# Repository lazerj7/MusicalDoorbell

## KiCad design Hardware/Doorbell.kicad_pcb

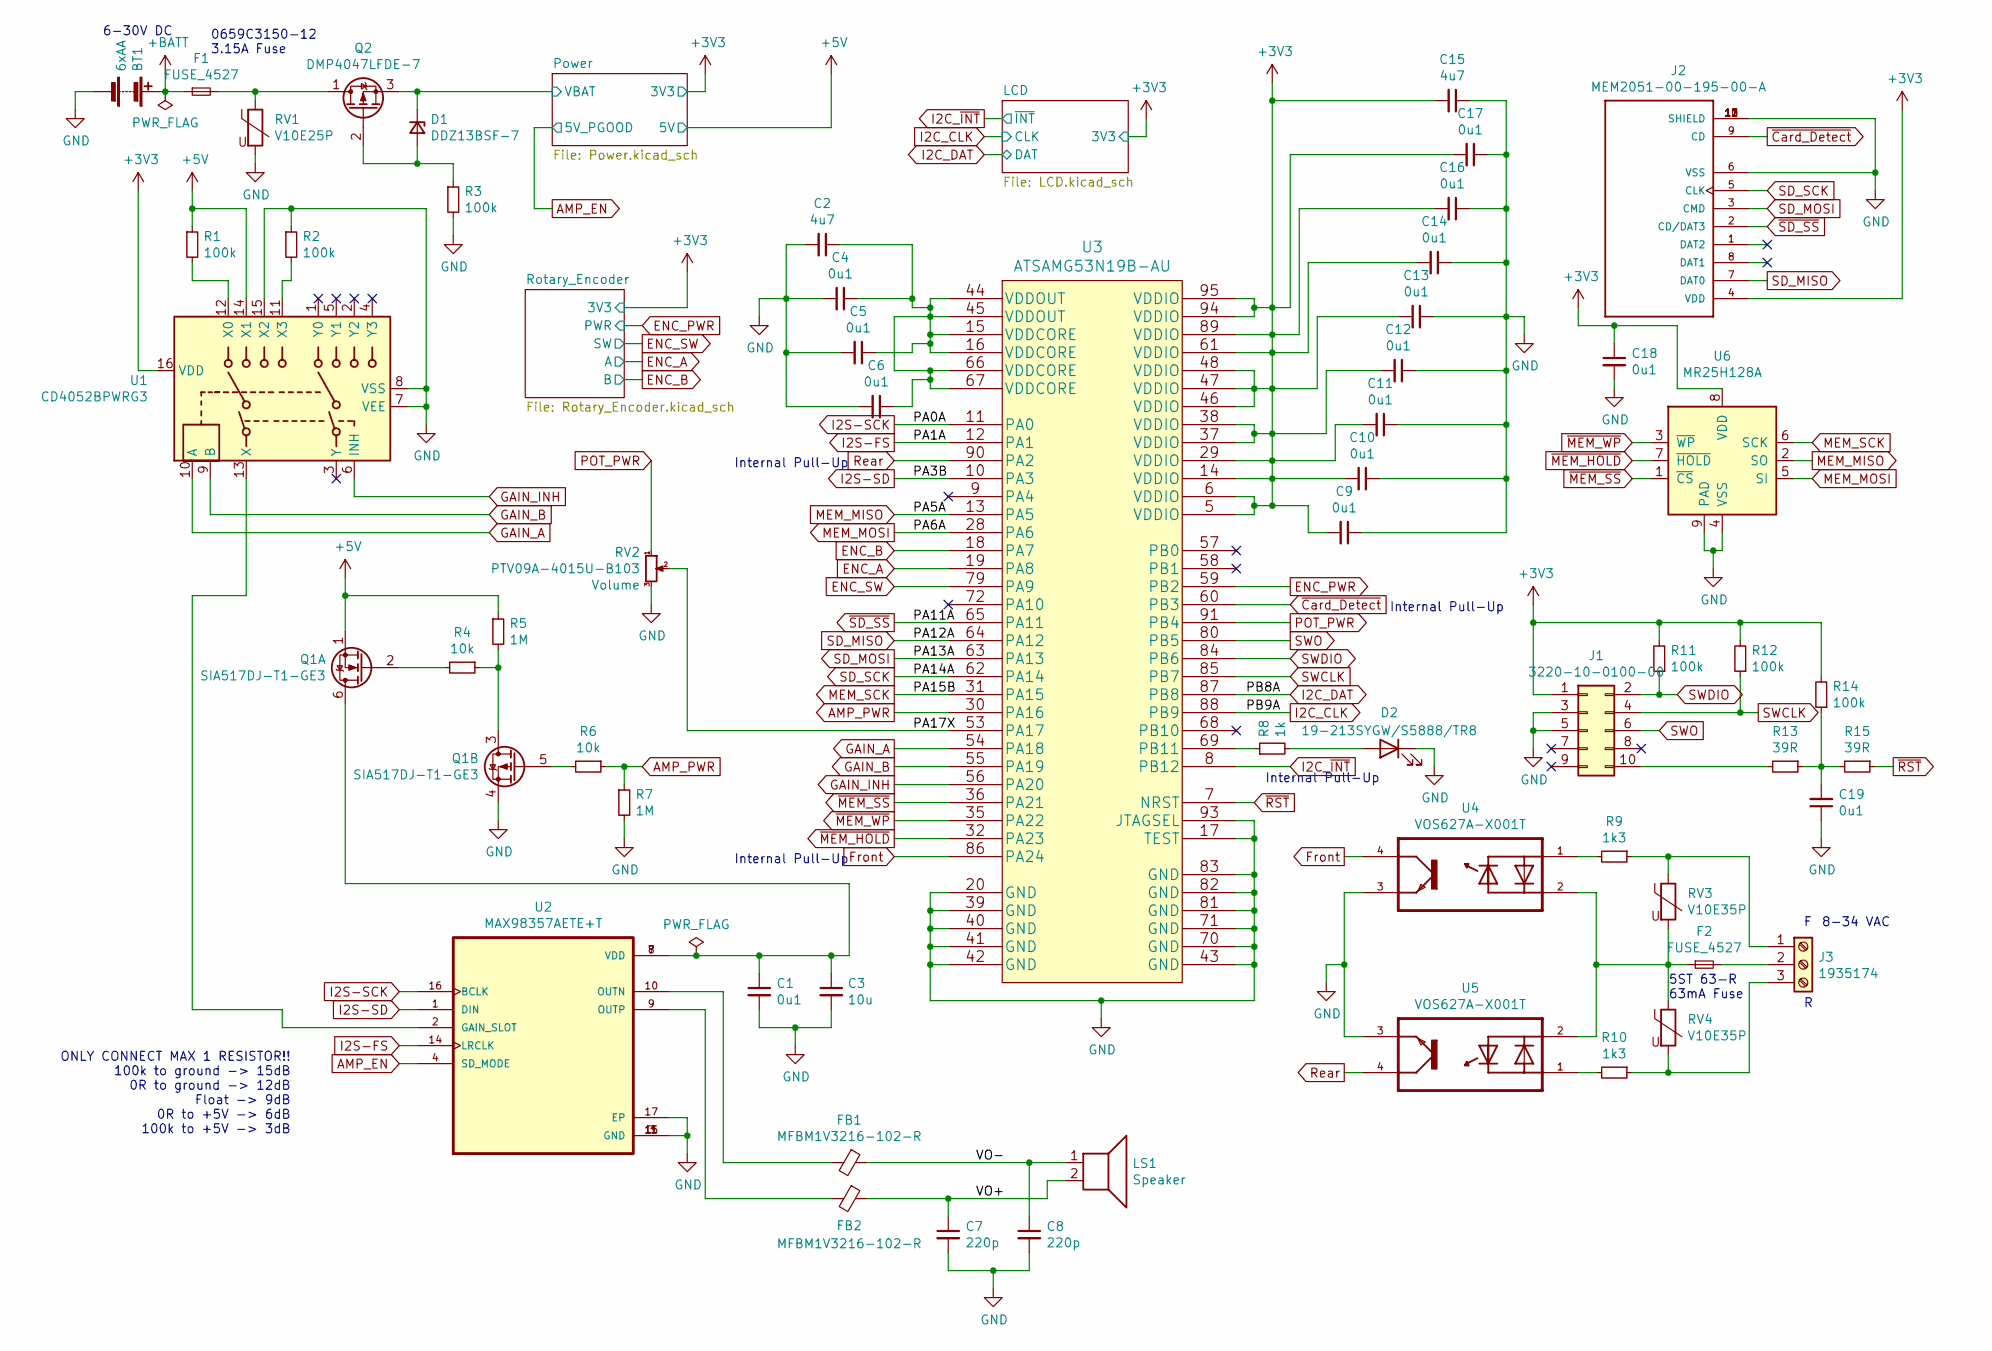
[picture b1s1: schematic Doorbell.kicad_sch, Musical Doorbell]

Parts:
BT1: 6xAA; Molex_MicroClasp_55935-0210_1x02_P2.00mm_Horizontal
C1, C4, C5, C6, C9, C10, C11, C12, C13, C14, C16, C17, C18, C19: 0u1; C_0603_1608Metric_Pad1.08x0.95mm_HandSolder
C2, C15: 4u7; C_1206_3216Metric_Pad1.33x1.80mm_HandSolder
C3: 10u; C_1206_3216Metric_Pad1.33x1.80mm_HandSolder
C7, C8: 220p; C_0603_1608Metric_Pad1.08x0.95mm_HandSolder
D1: DDZ13BSF-7; D_SOD-323_HandSoldering
D2: 19-213SYGW/S5888/TR8; LED_0603_1608Metric_Pad1.05x0.95mm_HandSolder
F1, F2: FUSE_4527
FB1, FB2: MFBM1V3216-102-R; L_1206_3216Metric_Pad1.42x1.75mm_HandSolder
J1: 3220-10-0100-00
J2: MEM2051-00-195-00-A
J3: 1935174; TerminalBlock_Phoenix_PT-1,5-3-5.0-H_1x03_P5.00mm_Horizontal
LS1: Speaker; Molex_MicroClasp_55935-0210_1x02_P2.00mm_Horizontal
Q1: SIA517DJ-T1-GE3; Vishay_PowerPAK_SC70-6L_Dual
Q2: DMP4047LFDE-7
R1, R2, R3, R11, R12, R14: 100k; R_0603_1608Metric_Pad0.98x0.95mm_HandSolder
R4, R6: 10k; R_0603_1608Metric_Pad0.98x0.95mm_HandSolder
R5, R7: 1M; R_0603_1608Metric_Pad0.98x0.95mm_HandSolder
R8: 1k; R_1206_3216Metric_Pad1.30x1.75mm_HandSolder
R9, R10: 1k3; 35501K3FT
R13, R15: 39R; R_0805_2012Metric_Pad1.20x1.40mm_HandSolder
RV1: V10E25P; RV_Disc_D12mm_W5.1mm_P7.5mm
RV2: PTV09A-4015U-B103
RV3, RV4: V10E35P; RV_Disc_D12mm_W5.8mm_P7.5mm
U1: CD4052BPWRG3; TSSOP-16_4.4x5mm_P0.65mm
U2: MAX98357AETE+T; MAX98357AETE_T
U3: ATSAMG53N19B-AU
U4, U5: VOS627A-X001T
U6: MR25H128A; DFN-8-1EP_6x5mm_P1.27mm_EP2x2mm

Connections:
+3V3: C9.2, C10.2, C11.2, C12.2, C13.2, C14.2, C15.2, C16.2, C17.2, C18.1, J1.1, J2.4 (VDD), R11.2, R12.2, R14.2, U1.16 (VDD), U3.5 (VDDIO), U3.6 (VDDIO), U3.14 (VDDIO), U3.29 (VDDIO), U3.37 (VDDIO), U3.38 (VDDIO), U3.46 (VDDIO), U3.47 (VDDIO), U3.48 (VDDIO), U3.61 (VDDIO), U3.89 (VDDIO), U3.94 (VDDIO), U3.95 (VDDIO), U6.8 (VDD); also elsewhere on the board
+5V: Q1.1 (S2), R1.1, R5.1, U1.14 (X1); also elsewhere on the board
+BATT: BT1.1 (+), F1.1
/PA17X: RV2.2, U3.53 (PA17)
/Power/VBAT: D1.1 (K), Q2.3 (S); also elsewhere on the board
/VO+: C7.1, FB2.1, LS1.2
/VO-: C8.1, FB1.1, LS1.1
AMP_EN: U2.4 (SD_MODE); also elsewhere on the board
AMP_PWR: R6.1, R7.1, U3.30 (PA16)
ENC_A: U3.19 (PA8); also elsewhere on the board
ENC_B: U3.18 (PA7); also elsewhere on the board
ENC_PWR: U3.59 (PB2); also elsewhere on the board
ENC_SW: U3.79 (PA9); also elsewhere on the board
Front: U3.86 (PA24), U4.4
GAIN_A: U1.10 (A), U3.54 (PA18)
GAIN_B: U1.9 (B), U3.55 (PA19)
GAIN_INH: U1.6 (INH), U3.56 (PA20)
GND: BT1.2 (-), C1.2, C2.2, C3.2, C4.2, C5.2, C6.2, C7.2, C8.2, C9.1, C10.1, C11.1, C12.1, C13.1, C14.1, C15.1, C16.1, C17.1, C18.2, C19.1, D2.1 (K), J1.3, J1.5, J2.6 (VSS), J2.10 (SHIELD), J2.11 (SHIELD), J2.12 (SHIELD), J2.13 (SHIELD), Q1.4 (S2), R2.1, R3.2, R7.2, RV1.2, RV2.3, RV2.4, RV2.5, U1.7 (VEE), U1.8 (VSS), U1.15 (X2), U2.3 (GND), U2.11 (GND), U2.15 (GND), U2.17 (EP), U3.17 (TEST), U3.20 (GND), U3.39 (GND), U3.40 (GND), U3.41 (GND), U3.42 (GND), U3.43 (GND), U3.70 (GND), U3.71 (GND), U3.81 (GND), U3.82 (GND), U3.83 (GND), U3.93 (JTAGSEL), U4.3, U5.3, U6.4 (VSS), U6.9 (PAD); also elsewhere on the board
I2C_CLK: U3.88 (PB9); also elsewhere on the board
I2C_DAT: U3.87 (PB8); also elsewhere on the board
I2C_~INT: U3.8 (PB12); also elsewhere on the board
I2S-FS: U2.14 (LRCLK), U3.12 (PA1)
I2S-SCK: U2.16 (BCLK), U3.11 (PA0)
I2S-SD: U2.1 (DIN), U3.10 (PA3)
MEM_MISO: U3.13 (PA5), U6.2 (SO)
MEM_MOSI: U3.28 (PA6), U6.5 (SI)
MEM_SCK: U3.31 (PA15), U6.6 (SCK)
unnamed: C1.1, C3.1, Q1.6 (D2), U2.7 (VDD), U2.8 (VDD)
unnamed: C2.1, C4.1, C5.1, C6.1, U3.15 (VDDCORE), U3.16 (VDDCORE), U3.44 (VDDOUT), U3.45 (VDDOUT), U3.66 (VDDCORE), U3.67 (VDDCORE)
unnamed: C19.2, R13.1, R14.1, R15.2
unnamed: D1.2 (A), Q2.2 (G), R3.1
unnamed: D2.2 (A), R8.2
unnamed: F1.2, Q2.1 (D), RV1.1
unnamed: F2.1, RV3.2, RV4.1, U4.2, U5.2
unnamed: F2.2, J3.2
unnamed: FB1.2, U2.10 (OUTN)
unnamed: FB2.2, U2.9 (OUTP)
unnamed: J1.10, R13.2
unnamed: J3.1, R9.1, RV3.1
unnamed: J3.3, R10.1, RV4.2
unnamed: Q1.2 (G2), R4.2
unnamed: Q1.3 (D2), R4.1, R5.2
unnamed: Q1.5 (G2), R6.2
unnamed: R1.2, U1.12 (X0)
unnamed: R2.2, U1.11 (X3)
unnamed: R8.1, U3.69 (PB11)
unnamed: R9.2, U4.1
unnamed: R10.2, U5.1
unnamed: U1.13 (X), U2.2 (GAIN_SLOT)
POT_PWR: RV2.1, U3.91 (PB4)
Rear: U3.90 (PA2), U5.4
SD_MISO: J2.7 (DAT0), U3.64 (PA12)
SD_MOSI: J2.3 (CMD), U3.63 (PA13)
SD_SCK: J2.5 (CLK), U3.62 (PA14)
SWCLK: J1.4, R12.1, U3.85 (PB7)
SWDIO: J1.2, R11.1, U3.84 (PB6)
SWO: J1.6, U3.80 (PB5)
~Card_Detect: J2.9 (CD), U3.60 (PB3)
~MEM_HOLD: U3.32 (PA23), U6.7 (~HOLD)
~MEM_SS: U3.36 (PA21), U6.1 (~CS)
~MEM_WP: U3.35 (PA22), U6.3 (~WP)
~RST: R15.1, U3.7 (NRST)
~SD_SS: J2.2 (CD/DAT3), U3.65 (PA11)

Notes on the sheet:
Internal Pull-Up
6-30V DC
8-34 VAC
0659C3150-12 3.15A Fuse
ONLY CONNECT MAX 1 RESISTOR!! 100k to ground -> 15dB 0R to ground -> 12dB Float -> 9dB 0R to +5V -> 6dB 100k to +5V -> 3dB
5ST 63-R 63mA Fuse

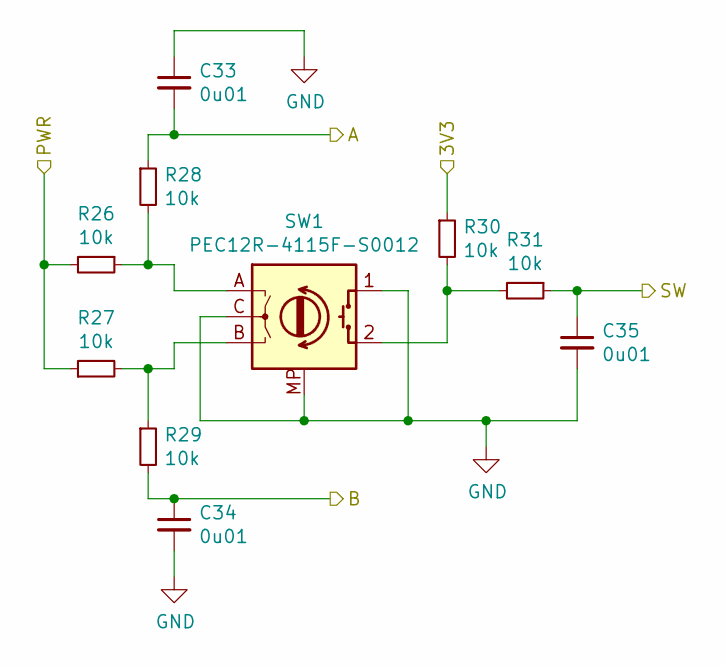
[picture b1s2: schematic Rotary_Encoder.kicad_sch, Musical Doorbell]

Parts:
C33, C34, C35: 0u01; C_0603_1608Metric_Pad1.08x0.95mm_HandSolder
R26, R27, R28, R29, R30, R31: 10k; R_0603_1608Metric_Pad0.98x0.95mm_HandSolder
SW1: PEC12R-4115F-S0012

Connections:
+3V3: R30.1; also elsewhere on the board
ENC_A: C33.2, R28.1; also elsewhere on the board
ENC_B: C34.1, R29.2; also elsewhere on the board
ENC_PWR: R26.2, R27.1; also elsewhere on the board
ENC_SW: C35.1, R31.1; also elsewhere on the board
GND: C33.1, C34.2, C35.2, SW1.1, SW1.C, SW1.MP; also elsewhere on the board
unnamed: R26.1, R28.2, SW1.A
unnamed: R27.2, R29.1, SW1.B
unnamed: R30.2, R31.2, SW1.2

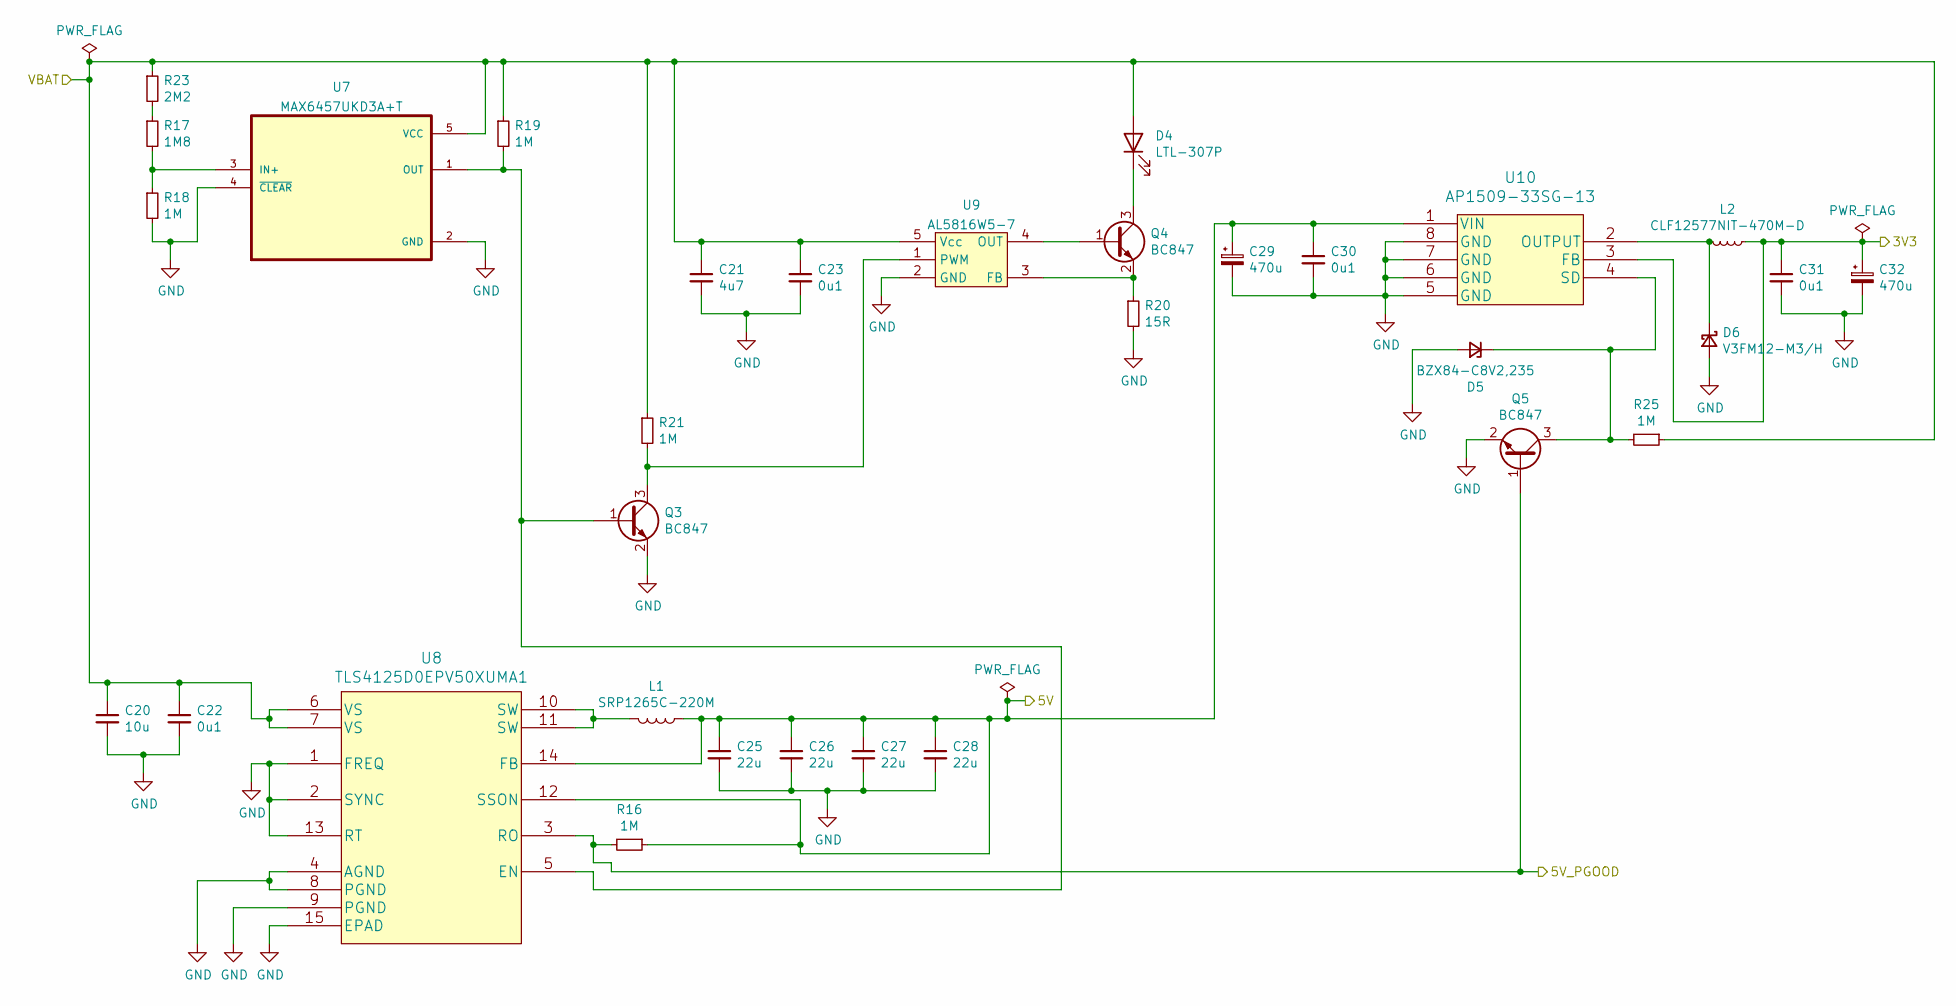
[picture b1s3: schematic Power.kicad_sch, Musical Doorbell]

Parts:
C20: 10u; C_1206_3216Metric_Pad1.33x1.80mm_HandSolder
C21: 4u7; C_1206_3216Metric_Pad1.33x1.80mm_HandSolder
C22, C23, C30, C31: 0u1; C_0603_1608Metric_Pad1.08x0.95mm_HandSolder
C25, C26, C27, C28: 22u; C_1210_3225Metric_Pad1.33x2.70mm_HandSolder
C29, C32: 470u; EEH-AZK1E471B
D4: LTL-307P
D5: BZX84-C8V2,235; D_SOT-23_ANK
D6: V3FM12-M3/H; V3FM12-M3_H
L1: SRP1265C-220M
L2: CLF12577NIT-470M-D
Q3, Q4, Q5: BC847; SOT-23
R16, R18, R19, R21, R25: 1M; R_0603_1608Metric_Pad0.98x0.95mm_HandSolder
R17: 1M8; R_0805_2012Metric_Pad1.20x1.40mm_HandSolder
R20: 15R; R_0805_2012Metric_Pad1.20x1.40mm_HandSolder
R23: 2M2; R_0603_1608Metric_Pad0.98x0.95mm_HandSolder
U7: MAX6457UKD3A+T
U8: TLS4125D0EPV50XUMA1
U9: AL5816W5-7
U10: AP1509-33SG-13

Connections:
+3V3: C31.1, C32.1, L2.1, U10.3 (FB); also elsewhere on the board
+5V: C25.1, C26.1, C27.1, C28.1, C29.1, C30.1, L1.1, R16.1, U8.12 (SSON), U8.14 (FB), U10.1 (VIN); also elsewhere on the board
/Power/VBAT: C20.1, C21.1, C22.1, C23.1, D4.2 (A), R19.1, R21.1, R23.1, R25.1, U7.5 (VCC), U8.6 (VS), U8.7 (VS), U9.5 (Vcc); also elsewhere on the board
AMP_EN: Q5.1 (B), R16.2, U8.3 (RO); also elsewhere on the board
GND: C20.2, C21.2, C22.2, C23.2, C25.2, C26.2, C27.2, C28.2, C29.2, C30.2, C31.2, C32.2, D5.2 (A), D6.2 (A), Q3.2 (E), Q5.2 (E), R18.2, R20.2, U7.2 (GND), U7.4 (~CLEAR), U8.1 (FREQ), U8.2 (SYNC), U8.4 (AGND), U8.8 (PGND), U8.9 (PGND), U8.13 (RT), U8.15 (EPAD), U9.2 (GND), U10.5 (GND), U10.6 (GND), U10.7 (GND), U10.8 (GND); also elsewhere on the board
unnamed: D4.1 (K), Q4.3 (C)
unnamed: D5.1 (K), Q5.3 (C), R25.2, U10.4 (SD)
unnamed: D6.1 (K), L2.2, U10.2 (OUTPUT)
unnamed: L1.2, U8.10 (SW), U8.11 (SW)
unnamed: Q3.1 (B), R19.2, U7.1 (OUT), U8.5 (EN)
unnamed: Q3.3 (C), R21.2, U9.1 (PWM)
unnamed: Q4.1 (B), U9.4 (OUT)
unnamed: Q4.2 (E), R20.1, U9.3 (FB)
unnamed: R17.1, R23.2
unnamed: R17.2, R18.1, U7.3 (IN+)

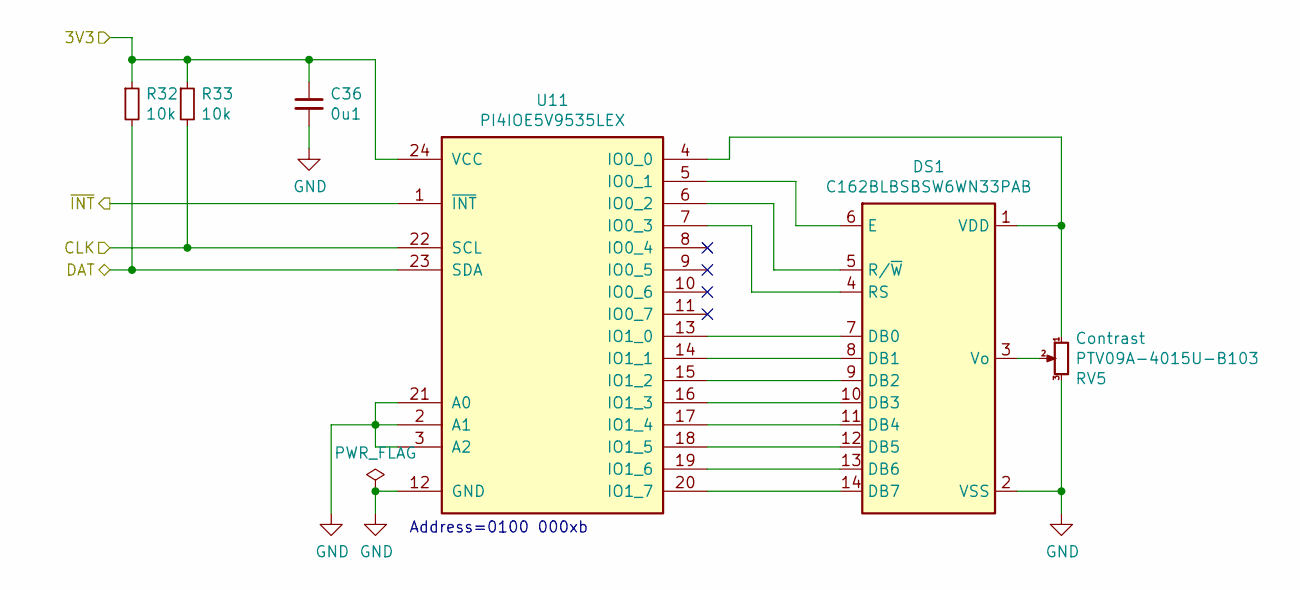
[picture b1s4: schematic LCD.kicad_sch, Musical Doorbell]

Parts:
C36: 0u1; C_0603_1608Metric_Pad1.08x0.95mm_HandSolder
DS1: C162BLBSBSW6WN33PAB
R32, R33: 10k; R_0603_1608Metric_Pad0.98x0.95mm_HandSolder
RV5: PTV09A-4015U-B103
U11: PI4IOE5V9535LEX; TSSOP-24_4.4x7.8mm_P0.65mm

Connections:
+3V3: C36.1, R32.1, R33.1, U11.24 (VCC); also elsewhere on the board
GND: C36.2, DS1.2 (VSS), RV5.3, RV5.4, RV5.5, U11.2 (A1), U11.3 (A2), U11.12 (GND), U11.21 (A0); also elsewhere on the board
I2C_CLK: R33.2, U11.22 (SCL); also elsewhere on the board
I2C_DAT: R32.2, U11.23 (SDA); also elsewhere on the board
I2C_~INT: U11.1 (~INT); also elsewhere on the board
unnamed: DS1.1 (VDD), RV5.1, U11.4 (IO0_0)
unnamed: DS1.3 (Vo), RV5.2
unnamed: DS1.4 (RS), U11.7 (IO0_3)
unnamed: DS1.5 (R/~W), U11.6 (IO0_2)
unnamed: DS1.6 (E), U11.5 (IO0_1)
unnamed: DS1.7 (DB0), U11.13 (IO1_0)
unnamed: DS1.8 (DB1), U11.14 (IO1_1)
unnamed: DS1.9 (DB2), U11.15 (IO1_2)
unnamed: DS1.10 (DB3), U11.16 (IO1_3)
unnamed: DS1.11 (DB4), U11.17 (IO1_4)
unnamed: DS1.12 (DB5), U11.18 (IO1_5)
unnamed: DS1.13 (DB6), U11.19 (IO1_6)
unnamed: DS1.14 (DB7), U11.20 (IO1_7)

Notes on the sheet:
Address=0100 000xb

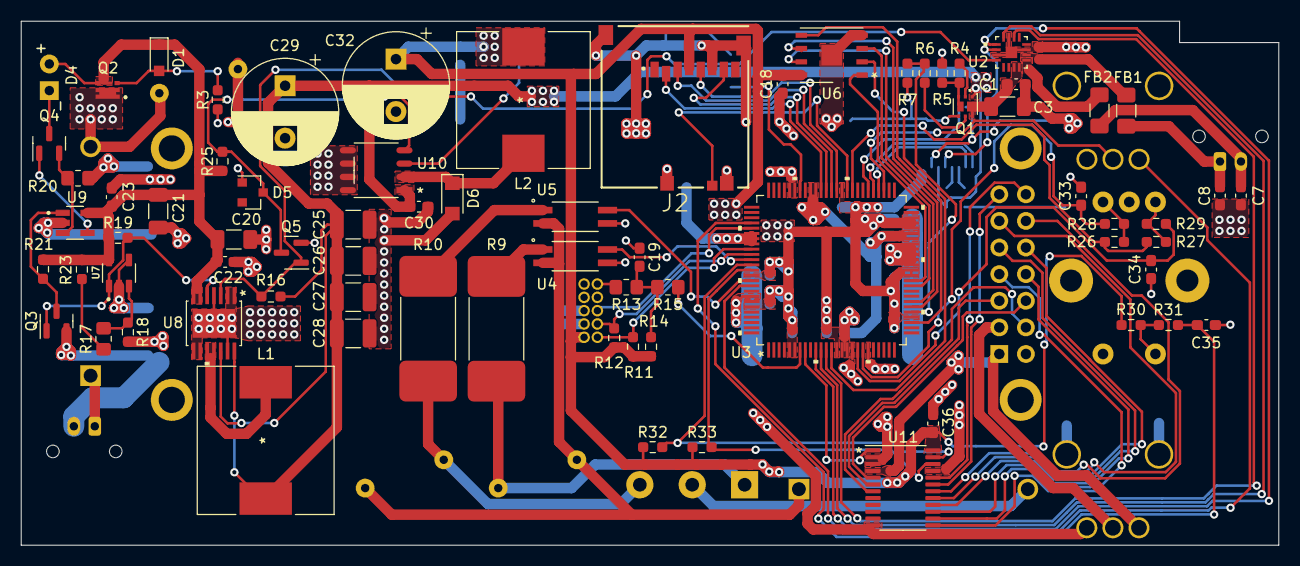
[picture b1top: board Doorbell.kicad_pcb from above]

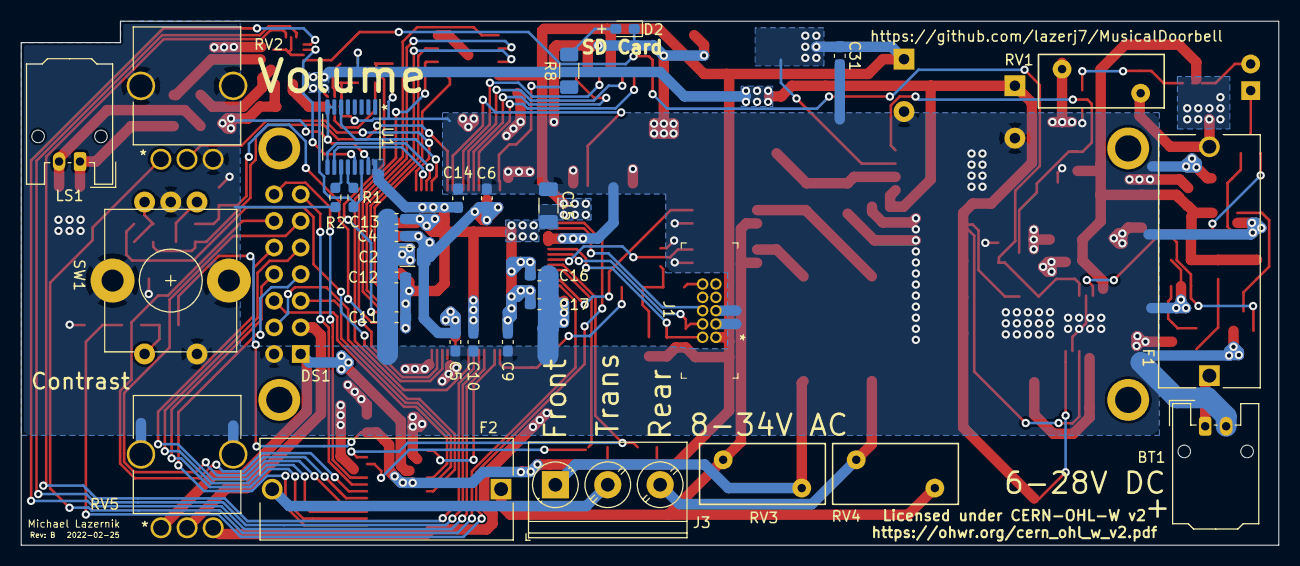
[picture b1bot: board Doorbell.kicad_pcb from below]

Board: 2 copper layers, 120.0 x 50.0 mm, 105 parts (32 on the bottom side), 89 nets.

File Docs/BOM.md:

# Bill of Materials

|Reference|Description|Part Number|Manufacturer|Quantity|
|---------|-----------|-----------|------------|--------|
|**Capacitors**|
|C1, C4, C5, C6, C9, C10, C11, C12, C13, C14, C16, C17, C18, C19, C22, C23, C30, C31, C36|0.1uF, 50V Ceramic Capacitor, SMD, 0603|CL10B104KB8NNNL|Samsung|19|
|C2, C15, C21|4.7uF, 50V Ceramic Capacitor, SMD, 1206|CL31B475KBHNNNE|Samsung|3|
|C3, C20|10uF, 50V Ceramic Capacitor, SMD, 1206|CL31B106KBHNNNE|Samsung|2|
|C7, C8|220pF, 50V Ceramic Capacitor, SMD, 0603|CL10B221KB8NFNC|Samsung|2|
|C24|1uF, 25V Ceramic Capacitor, SMD, 0603|CL10B105KA8NFNC|Samsung|1|
|C25, C26, C27, C28|22uF, 25V Ceramic Capacitor, SMD, 1210|CL32B226KAJNNWE|Samsung|4|
|C29, C32|470uF, 25V Polymer Capacitor|EEH-AZK1E471B|Panasonic|2|
|C33, C34, C35|0.01uF, 50V Ceramic, SMD, 0603|CL10B103KB8NNNC|Samsung|3|
|**Resistors**|
|R1, R2, R3, R11, R12, R14|100k Resistor, SMD, 0603, 1/10W, 1%|CRCW0603100KFKEAC|Vishay|6|
|R4, R6, R26, R27, R28, R29, R30, R31, R32, R33, R34|10k Resistor, SMD, 0603, 1/10W, 1%|CRCW060310K0FKECC|Vishay|11|
|R5, R7, R16, R20, R22, R25|1M Resistor, SMD, 0603, 1/10W, 1%|CRCW06031M00FKEA|Vishay|6|
|R8|1k Resistor, SMD, 1206, 1/4W, 1%|CRCW12061K00FKEBC|Vishay|1|
|R9, R10|1.3K Resistor, SMD, 5W, 1%|35501K3FT|TE Connectivity|2|
|R13, R15|39 Ohm Resistor, SMD, 0805, 1/2W, 5%|ERJ-P06J390V|Panasonic|2|
|R17|1.8M Resistor, SMD, 0805, 1/10W, 0.1%|CPF0805B1M8E|TE Connectivity|1|
|R18|1.3M Resistor, SMD, 0805, 1/10W, 0.1%|CPF0805B1M3E1|TE Connectivity|1|
|R19|10M Resistor, SMD, 0805, 1/8W, 0.5%|CRCW080510M0DHEAP|Vishay|1|
|R21, R23|2.2k Resistor, SMD, 0603, 1/10W, 1%|CRCW06032K20FKEAC|Vishay|2|
|R24|180 Ohm Resistor, SMD, 0805, 1/8W, 0.5%|ERA-6AED181V|Panasonic|1|
|**Potentiometers**|
|RV2, RV5|10K Potentiometer, 1/20W|PTV09A-4015U-B103|Bourns|2|
|**LEDs**|
|D2|Yellow/Green SMD LED|19-213SYGW/S5888/TR8|Everlight Electronics|1|
|D4|Red LED|LTL-307P|LITEON|1|
|**Diodes**|
|D1|Zener Diode, 12.88V, 500mW|DDZ13BSF-7|Diodes Inc|1|
|D3, D5|Zener Diode, 8.2V, 250mW|BZX84-C8V2,235|Nexperia|2|
|D6|Schottky Diode|V3FM12-M3/H|Vishay|1|
|**Inductors**|
|FB1, FB2|Ferrite Bead|MFBM1V3216-102-R|Eaton|2|
|L1|22uH Inductor|SRP1265C-220M|Bourns|1|
|L2|47uH Inductor|CLF12577NIT-470M-D|TDK|1|
|**Transistors**|
|Q1|N-CH/P-CH Dual MOSFET, 12V, 4.5A|SIA517DJ-T1-GE3|Vishay|1|
|Q2|P-CH MOSFET, 40V, 3.3A|DMP4047LFDE-7|Diodes Inc|1|
|Q3|P-CH MOSFET, 30V, 4A|PMPB47XP|Nexperia|1|
|Q4, Q5|NPN BJT, 45V, 100mA|BC847,215|Nexperia|2|
|**IC’s**|
|U1|Mux/Demux 2x 4:1|CD4052BPWRG3|Texas Instruments|1|
|U2|Class D Amplifier|MAX98357AETE+T|Analog Devices (Maxim)|1|
|U3|MCU, ARM Cortex M4|ATSAMG53N19B-AU|Microchip|1|
|U4, U5|Optoisolator, A/C Input|VOS627A-X001T|Vishay|2|
|U6|MRAM Module, 128kb (16kx8), SPI|MR25H128A|Everspin Technologies|1|
|U7|2.5V Voltage Reference|LT6654BHS6-2.5#TRMPBF|Analog Devices|1|
|U8|Switching Regulator, Buck, 5V, 2.5A|TLS4125D0EPV50XUMA1|Infineon|1|
|U9|Dual Comparator|LM2903DR2G|onsemi|1|
|U10|Switching Regulator, Buck, 3.3V, 1A|AP1509-33SG-13|Diodes Inc|1|
|U11|IO Expander 16b, I2C|PI4IOE5V9535LEX|Diodes Inc|1|
|**Display**|
|DS1|Character LCD, 16x2|C162BLBSBSW6WN33PAB|Focus LCDs|1|
|**Connectors, Switches, Etc.**|
|F1, F2|Fuse Holder, 5mmx20mm Fuses|4527|Keystone Electronics|2|
|J1|SWD Connector|3220-10-0100-00|CNC Tech|1|
|J2|MircoSD Card Connector|MEM2051-00-195-00-A|GCT|1|
|J3|Doorbell Wire Terminal (3 Wire)|1935174|Phoenix Contact|1|
|(LS1)*|Speaker|3968|Adafruit|1|
|BT1, LS1|Wire Connector Terminal, 2 Pos|559350210|Molex|2|
|*|Wire Connector Housing, 2 Pos|513820200|Molex|2|
|*|Connector Wire Contact|561349100|Molex|4|
|SW1|Rotary Encoder|PEC12R-4115F-S0012|Bourns|1|
|(F1)*|3.15A Fuse, Ceramic, Slow Blow, 5mmx20mm|0659C3150-12|Bel Fuse|1|
|(F2)*|63mA Fuse, Glass, Slow Blow, 5mmx20mm|5ST 63-R|Bel Fuse|1|
|RV1|MOV, 39V 2kA|V10E25P|Littelfuse|1|
|RV3, RV4|MOV, 56V 2kA|V10E35P|Littelfuse|2|
|(DS1)*|Machine Screw, M2.5x0.45|29300|Keystone Electronics|4|
|(DS1)*|Standoff, M2.5x0.45, 11mm|M2106-2545-AL|RAF Electronic Hardware|4|
|(DS1)*|DS1 Pin Header|PREC007DAAN-RC|Sullins Connector|1|
|(DS1)*|DS1 Socket Header|PPTC072LFBN-RC|Sullins Connector|1|

*=Not on Schematic

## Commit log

2022-01-10 Clean up custom KiCad libraries
    - Clean up the directory structure for KiCad custom libraries.
    - Fix paths in KiCad schematic and pcb for symbols, footprints, and
    3d models for custom libraries.
2022-01-10 Cleanup custom KiCad libraries
    - Delete unneeded/unused files
    - Cleanup symbol library files for custom libraries
2022-01-11 Switch to local libraries for KiCad schematic
    - Move all KiCad schematic symbols into local libraries
    - Fix KiCad schematic library links to point to local libraries
2022-01-11 Move KiCad global footprint and 3d models to local
    - Move KiCad global footprint and 3d models to local directories
    - Reassign footprints in KiCad schematic/PCB from global libraries to
    local libraries
    - Reassign global 3d models to local 3d models for KiCad
    - Update KiCad PCB with all local footprints
2022-01-11 Cleanup silkscreen
    - Make sure component IDs are visible and clear
    - Make sure pin 1 of IC's has marker
    - Overall housekeeping of silkscreen layer
2022-01-13 Add some initial documentation and production files
    - Add BOM to Docs in ods, pdf, and md formats
    - Add Schematic to Docs in pdf format
    - Add PCB layouts to Docs in pdf format
    - Add 3D PCB images to Docs in png format
    - Add 3D PCB VRML/wrl file to Docs
    - Add component 3D models in step format to local libs in Hardware
2022-01-13 Fix .gitignore to ignore LibreOffice lock files
2022-01-13 Fix some minor formatting issues in BOM
    -Fix column heights in BOM.ods
    -Regenerate BOM.pdf from BOM.ods
2022-02-26 Bump to board revision B
    - Redesign low battery circuit
    - Replace comparator with PMIC
    - Utilize LED Driver IC
    - Remove unneeded 2.5v voltage reference
    - Reroute some signals onto wkup/external interrupt pins

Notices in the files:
Hardware/Doorbell.kicad_pcb:
Licensed under CERN-OHL-W v2
parts and their libraries:
Copyright 2021 Accelerated Designs. All rights reserved.
